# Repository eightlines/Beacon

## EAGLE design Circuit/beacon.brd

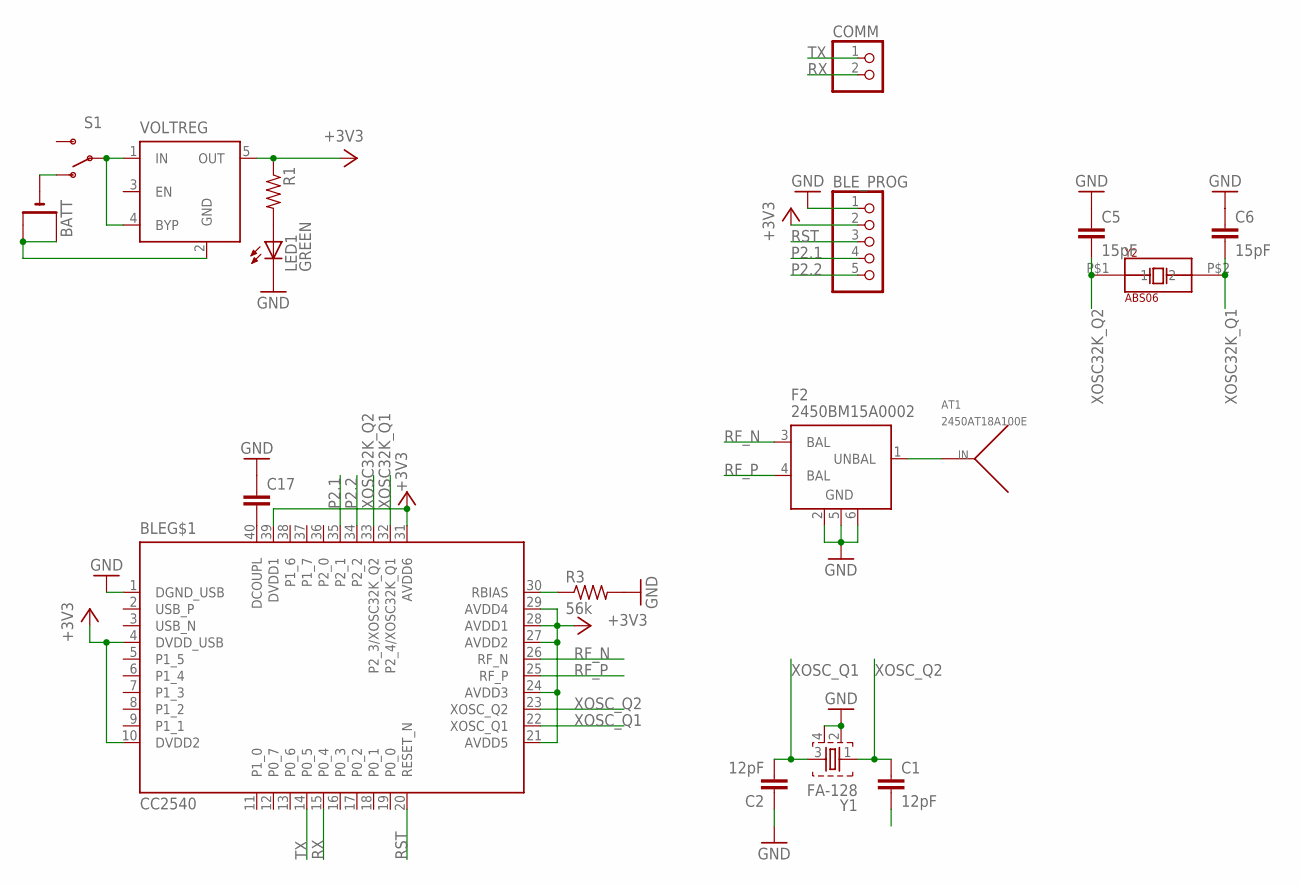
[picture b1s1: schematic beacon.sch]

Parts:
AT1: 2450AT18A100E
BATT: CR2032SMT; CR2032-SMD
BLE: CC2540; QFN40-6X6
BLE_PROG: PINHD-1X5; 1X05
C1, C2: 12pF; C0402
C5, C6: 15pF; C0402
C17: C-EUC0402; C0402
COMM: PINHD-1X2; 1X02
F2: 2450BM15A0002
LED1: GREEN; LED-0603
R1: RESISTOR0402-RES; 0402-RES
R3: 56k; R0402
S1: SWITCH-SPDT-SMD-A; SWITCH-SPST-SMD-A
VOLTREG: MIC5219XX; SOT23-5
Y1: FA-128
Y2: ABS06; SMD

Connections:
+3V3: BLE.4 (DVDD_USB), BLE.10 (DVDD2), BLE.21 (AVDD5), BLE.24 (AVDD3), BLE.27 (AVDD2), BLE.28 (AVDD1), BLE.29 (AVDD4), BLE.31 (AVDD6), BLE.39 (DVDD1), BLE_PROG.2, R1.1, VOLTREG.5 (OUT)
GND: BLE.1 (DGND_USB), BLE_PROG.1, C2.1, C5.1, C6.1, C17.1, F2.2 (GND), F2.5 (GND), F2.6 (GND), LED1.C, R3.2, Y1.2, Y1.4
unnamed: BLE.40 (DCOUPL), C17.2
unnamed: BLE.30 (RBIAS), R3.1
unnamed: LED1.A, R1.2
unnamed: AT1.P$1, F2.1 (UNBAL)
unnamed: BATT.-, S1.1 (O)
unnamed: S1.2, VOLTREG.1 (IN), VOLTREG.4 (BYP)
unnamed: BATT.+$1 (+), BATT.+$2 (+1), VOLTREG.2 (GND)
P2.1: BLE.35 (P2_1), BLE_PROG.4
P2.2: BLE.34 (P2_2), BLE_PROG.5
RF_N: BLE.26 (RF_N), F2.3 (BAL)
RF_P: BLE.25 (RF_P), F2.4 (BAL)
RST: BLE.20 (RESET_N), BLE_PROG.3
RX: BLE.15 (P0_4), COMM.2
TX: BLE.14 (P0_5), COMM.1
XOSC32K_Q1: BLE.32 (P2_4/XOSC32K_Q1), C6.2, Y2.P$2 (2)
XOSC32K_Q2: BLE.33 (P2_3/XOSC32K_Q2), C5.2, Y2.P$1 (1)
XOSC_Q1: BLE.22 (XOSC_Q1), C2.2, Y1.3
XOSC_Q2: BLE.23 (XOSC_Q2), C1.1, Y1.1

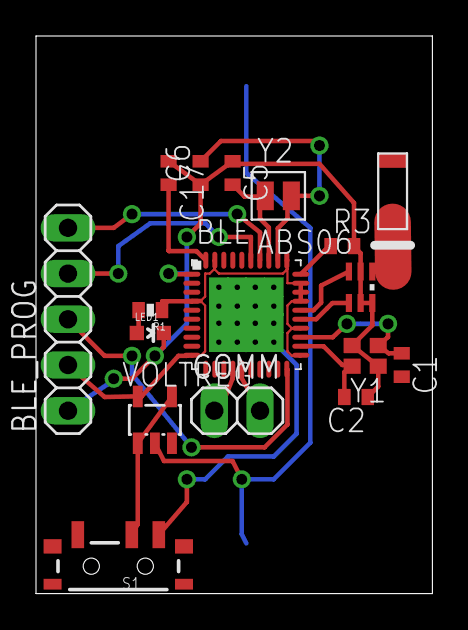
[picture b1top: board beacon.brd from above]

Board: 2 copper layers, 22.0 x 31.0 mm, 18 parts (1 on the bottom side), 20 nets.

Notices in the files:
parts and their libraries:
SparkFun-LED: Licensing: Creative Commons ShareAlike 4.0 International - https://creativecommons.org/licenses/by-sa/4.0
